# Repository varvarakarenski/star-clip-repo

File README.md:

# star-clip

KiCad files for a PCB hair clip I designed. I thought this would be a cute 'woman-in-STEM' accessory.
- What it is: a star-shaped clip with 6 LEDs that blink, driven by a 555 timer
and powered by ecoin cell batteries
- Cute features: Some of the code from my personal projects! (syntax neglected in favor of aesthetics) 
  Contains Python from my data analysis script for ion propulsion research, and JS from my iss-tracker project.
- Made on earth by humans.

## BOM

| Part | Value | Quantity |
|------|-------|----------|
| Coin cell battery holder (Keystone 3034, 20mm) | | 2 |
| Electrolytic capacitor (8mm radial) | (e.g. 10µF) | 2 |
| 5mm LED | | 6 |
| 2N3906 PNP transistor | | 2 |
| Resistor | 470Ω | 6 |
| Resistor | 4.7kΩ | 1 |
| Resistor | 47kΩ | 3 |
| LM555 timer (DIP-8) | | 1 |

## Schematic

## PCB

## 3D View

## Slack
@varvarakarenski

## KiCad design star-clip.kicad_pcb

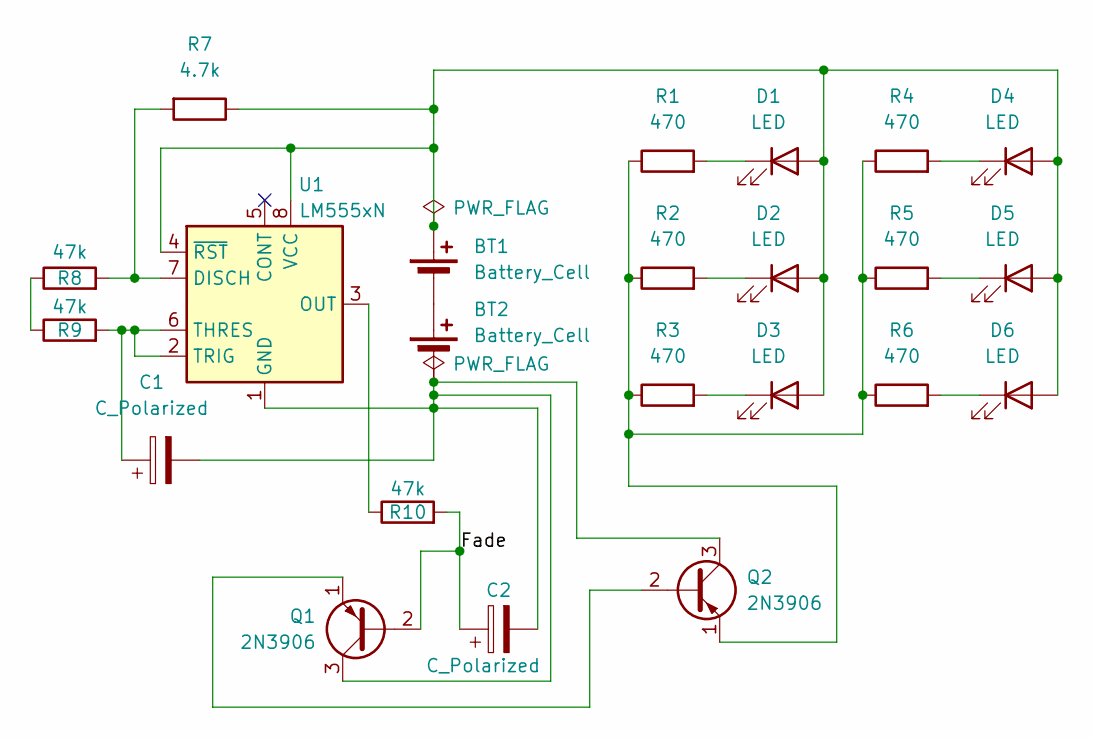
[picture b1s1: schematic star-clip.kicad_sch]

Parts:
BT1, BT2: Battery_Cell; BatteryHolder_Keystone_3034_1x20mm
C1, C2: C_Polarized; CP_Radial_D8.0mm_P5.00mm
D1, D2, D3, D4, D5, D6: LED; LED_D5.0mm
Q1, Q2: 2N3906; TO-92L_HandSolder
R1, R2, R3, R4, R5, R6: 470; R_Axial_DIN0207_L6.3mm_D2.5mm_P7.62mm_Horizontal
R7: 4.7k; R_Axial_DIN0207_L6.3mm_D2.5mm_P7.62mm_Horizontal
R8, R9, R10: 47k; R_Axial_DIN0207_L6.3mm_D2.5mm_P7.62mm_Horizontal
U1: LM555xN; DIP-8_W7.62mm

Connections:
/Fade: C2.1, Q1.2 (B), R10.2
unnamed: BT1.1 (+), D1.2 (A), D2.2 (A), D3.2 (A), D4.2 (A), D5.2 (A), D6.2 (A), R7.1, U1.4 (~RST), U1.8 (VCC)
unnamed: BT1.2 (-), BT2.1 (+)
unnamed: BT2.2 (-), C1.2, C2.2, Q1.3 (C), Q2.3 (C), U1.1 (GND)
unnamed: D1.1 (K), R1.2
unnamed: D2.1 (K), R2.2
unnamed: D3.1 (K), R3.2
unnamed: D4.1 (K), R4.2
unnamed: D5.1 (K), R5.2
unnamed: D6.1 (K), R6.2
unnamed: Q1.1 (E), Q2.2 (B)
unnamed: Q2.1 (E), R1.1, R2.1, R3.1, R4.1, R5.1, R6.1
unnamed: R8.1, R9.1
unnamed: R7.2, R8.2, U1.7 (DISCH)
unnamed: R10.1, U1.3 (OUT)
unnamed: C1.1, R9.2, U1.2 (TRIG), U1.6 (THRES)

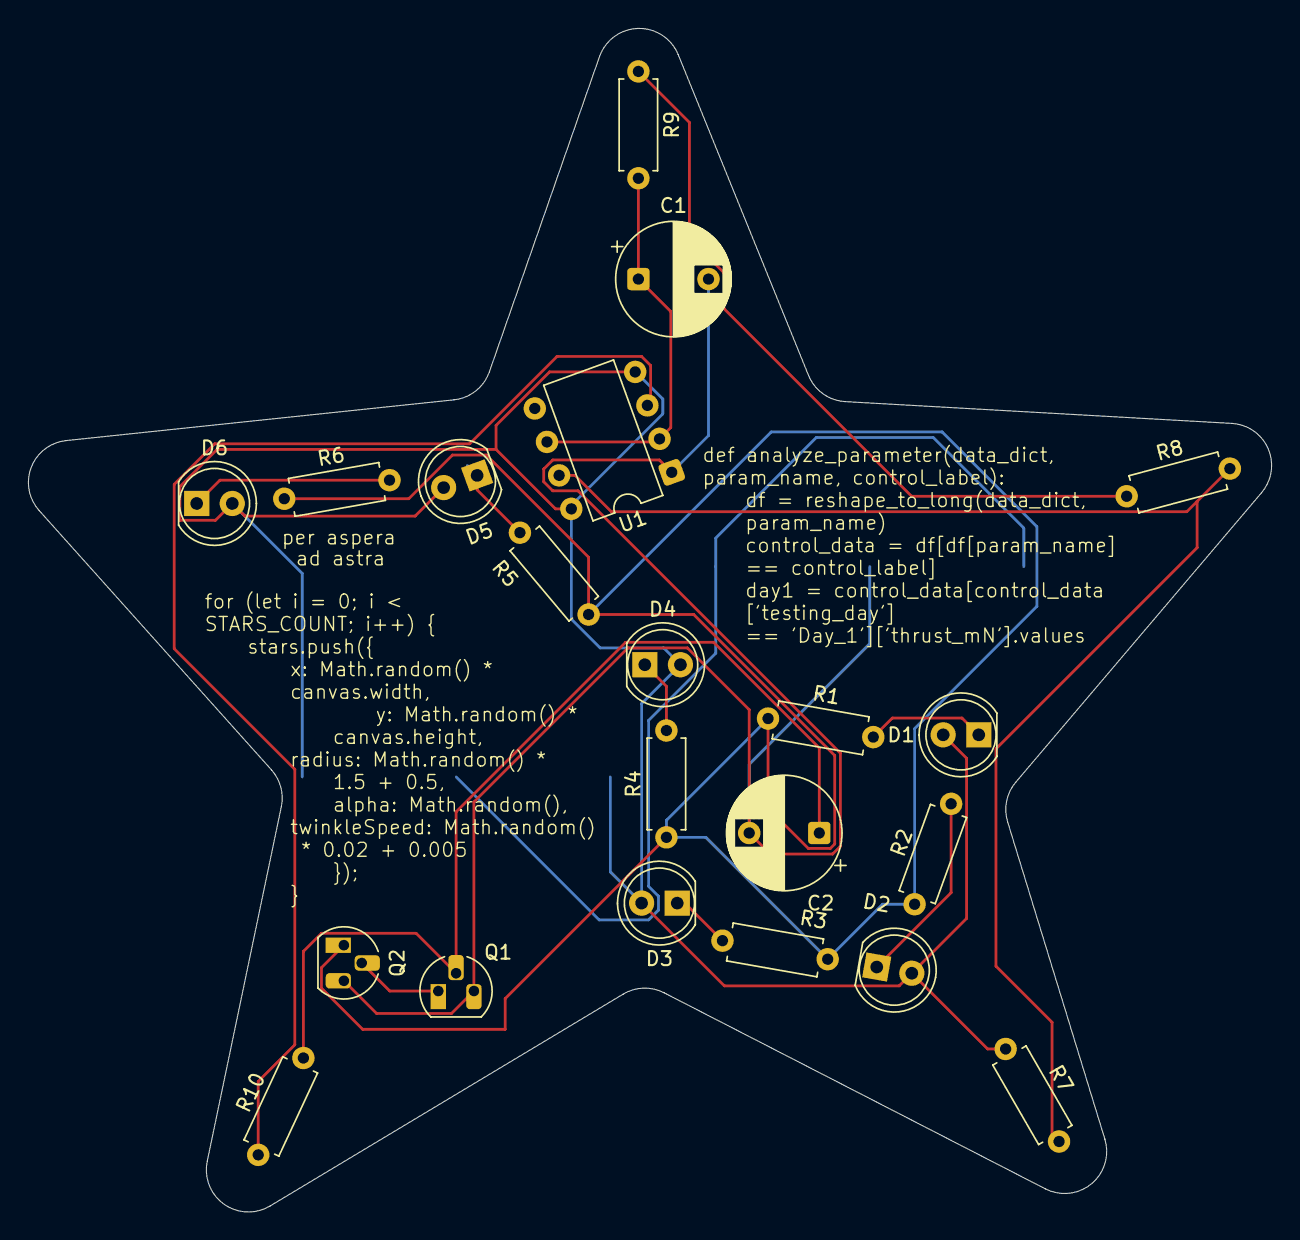
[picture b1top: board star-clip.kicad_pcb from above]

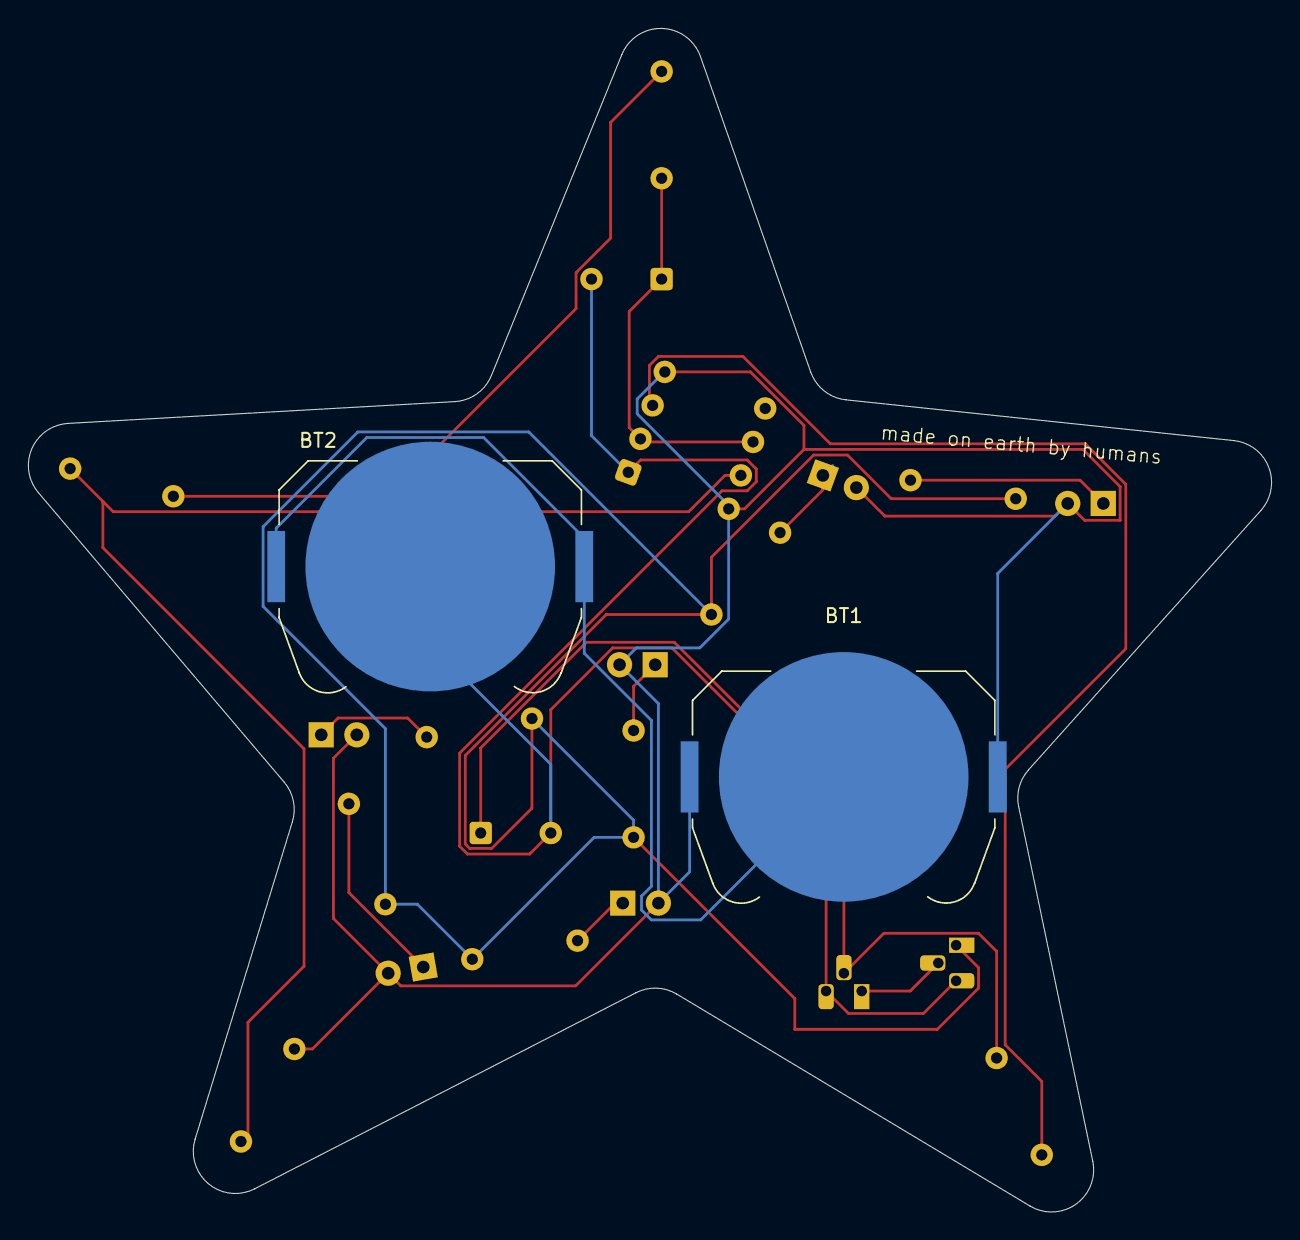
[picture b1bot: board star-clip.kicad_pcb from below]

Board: 2 copper layers, 88.7 x 84.4 mm, 23 parts (2 on the bottom side), 16 nets.

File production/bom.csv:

Designator,Footprint,Quantity,Value,LCSC Part #
"BT1, BT2",BatteryHolder_Keystone_3034_1x20mm,2,Battery_Cell,
"C1, C2",CP_Radial_D8.0mm_P5.00mm,2,C_Polarized,
"D1, D2, D3, D4, D5, D6",LED_D5.0mm,6,LED,
"Q1, Q2",TO-92L_HandSolder,2,2N3906,
"R1, R2, R3, R4, R5, R6",R_Axial_DIN0207_L6.3mm_D2.5mm_P7.62mm_Horizontal,6,470,
"R10, R8, R9",R_Axial_DIN0207_L6.3mm_D2.5mm_P7.62mm_Horizontal,3,47k,
R7,R_Axial_DIN0207_L6.3mm_D2.5mm_P7.62mm_Horizontal,1,4.7k,
U1,DIP-8_W7.62mm,1,LM555xN,
